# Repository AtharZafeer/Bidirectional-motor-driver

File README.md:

# Bidirectional-motor-driver
This contains the pcb layout and schematic of a bidirection H Bridge motor driver
This is created by me as a hobby

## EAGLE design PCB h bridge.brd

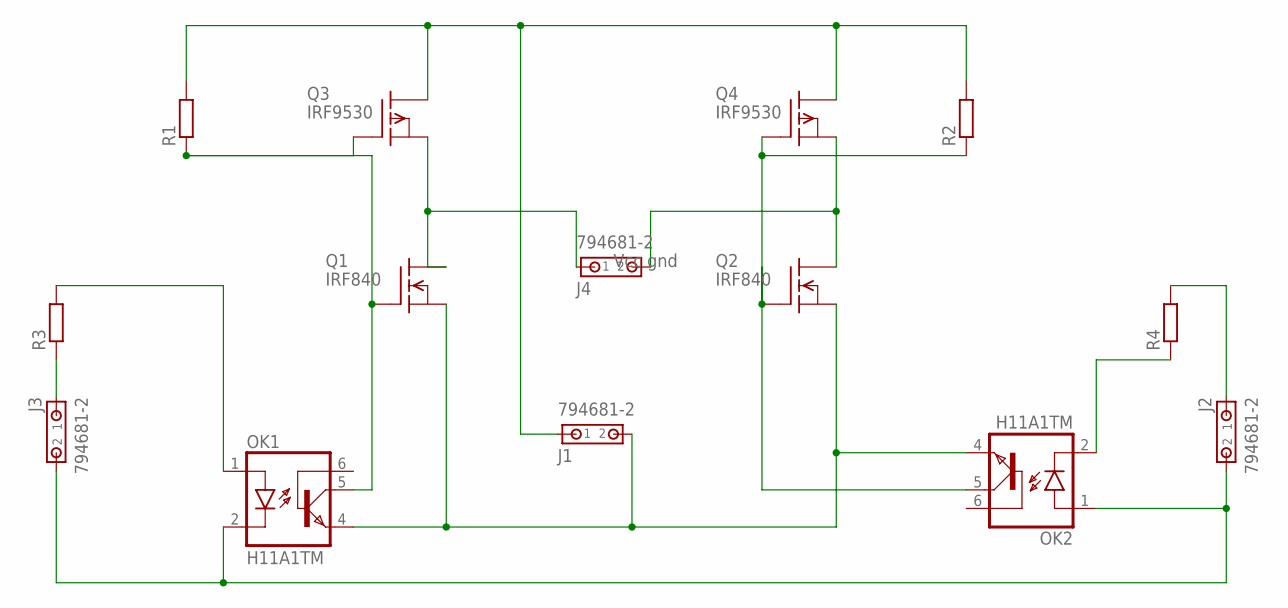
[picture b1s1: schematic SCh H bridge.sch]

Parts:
J1, J2, J3, J4: 794681-2
OK1, OK2: H11A1TM; DIL6-04
Q1, Q2: IRF840; TO220
Q3, Q4: IRF9530; TO220
R1, R2, R3, R4: R-EU_0309/12; 0309/12

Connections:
unnamed: J1.1, Q3.2 (D), Q4.2 (D), R1.2, R2.2
unnamed: J1.2, OK1.4 (EMI), OK2.4 (EMI), Q1.3 (S), Q2.3 (S)
unnamed: J4.2, Q2.2 (D), Q4.3 (S)
unnamed: OK2.5 (COL), Q2.1 (G), Q4.1 (G), R2.1
unnamed: OK1.5 (COL), Q1.1 (G), Q3.1 (G), R1.1
unnamed: OK2.2 (C), R4.1
unnamed: J2.1, R4.2
unnamed: J2.2, J3.2, OK1.2 (C), OK2.1 (A)
unnamed: J3.1, R3.1
unnamed: OK1.1 (A), R3.2
unnamed: J4.1, Q1.2 (D), Q3.3 (S)

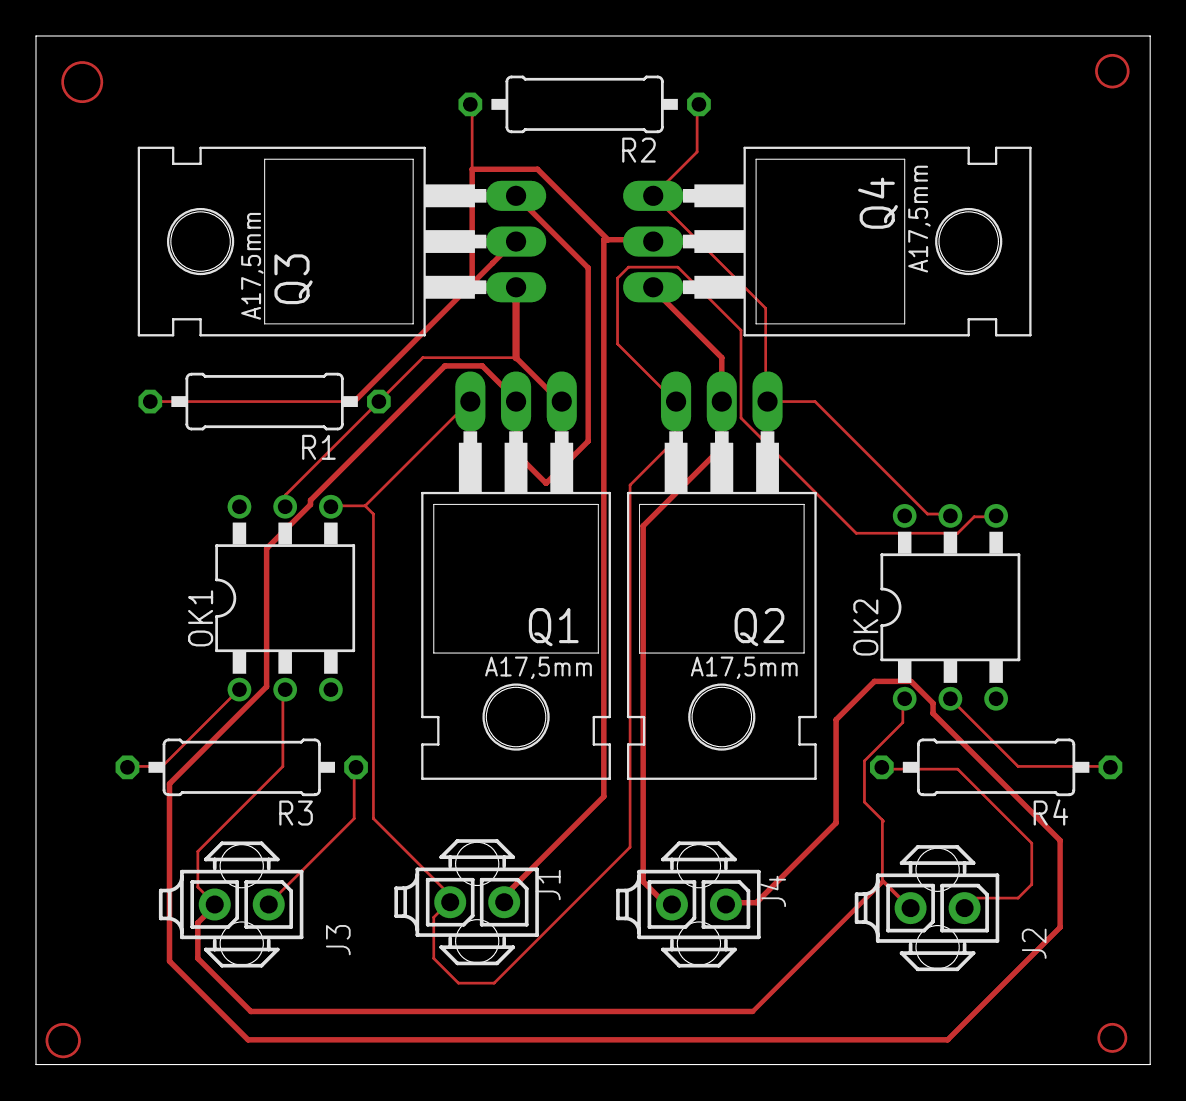
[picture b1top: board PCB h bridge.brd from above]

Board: 2 copper layers, 61.9 x 57.1 mm, 14 parts (0 on the bottom side), 11 nets.

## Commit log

2019-10-24 Add pcb, schematic and pdf file
